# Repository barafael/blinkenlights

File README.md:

# blinkenlights: Blink lights and control other things, controlled by up to 5 input channels

The purpose of this board is to read some standard RC PWM channels, and switch the output MOSFETs accordingly.
This can be used to blink lights on an RC airplane in patterns, for example. The input channel allows to switch between modes, like standard flying mode and Taxi/Standby modes. Or, a landing light can be switched on/off by a separate channel.
The channels can be either dedicated lines from the receiver, or just other lines which are in use anyway. For example, the throttle signal could be used to switch between standby and flying, and the landing flaps signal could turn on/off the landing lights.

It would be easily possible to dim lights using PWM, I just have not made use of that yet.

The code pretty much just reads the input channels and reads the state from them, and then passes that state (and a tick value) to a function for each output pin. The function can then decide to do whatever with the output pin.

RC PWM signal is read using interrupts, and the program detects when a signal has been disconnected, resetting the state accordingly. That means that you can attach, detach, and reattach PWM signals during operation as you like.

The I2C pins are still free and accessible, so it would be possible to hook up I2C sensors also, like a temperature sensor on the brakes or a barometer.

Input voltage goes directly to the Pro Mini internal regulator, that means it should be 3.3V-16V.

That input voltage is directly supplied to the output pins via the MOSFET driver: an IRLML6244TRPBF SOT-23 package which can switch up to 6.3A (according to datasheet, but I haven't stressed it like that yet).

The PCB is designed in KiCad.

If you have any suggestions or spot an error somewhere, please let me know!

Render of PCB:

PCB in pcbnew:

Schematic:

MOSFET driver schematic:

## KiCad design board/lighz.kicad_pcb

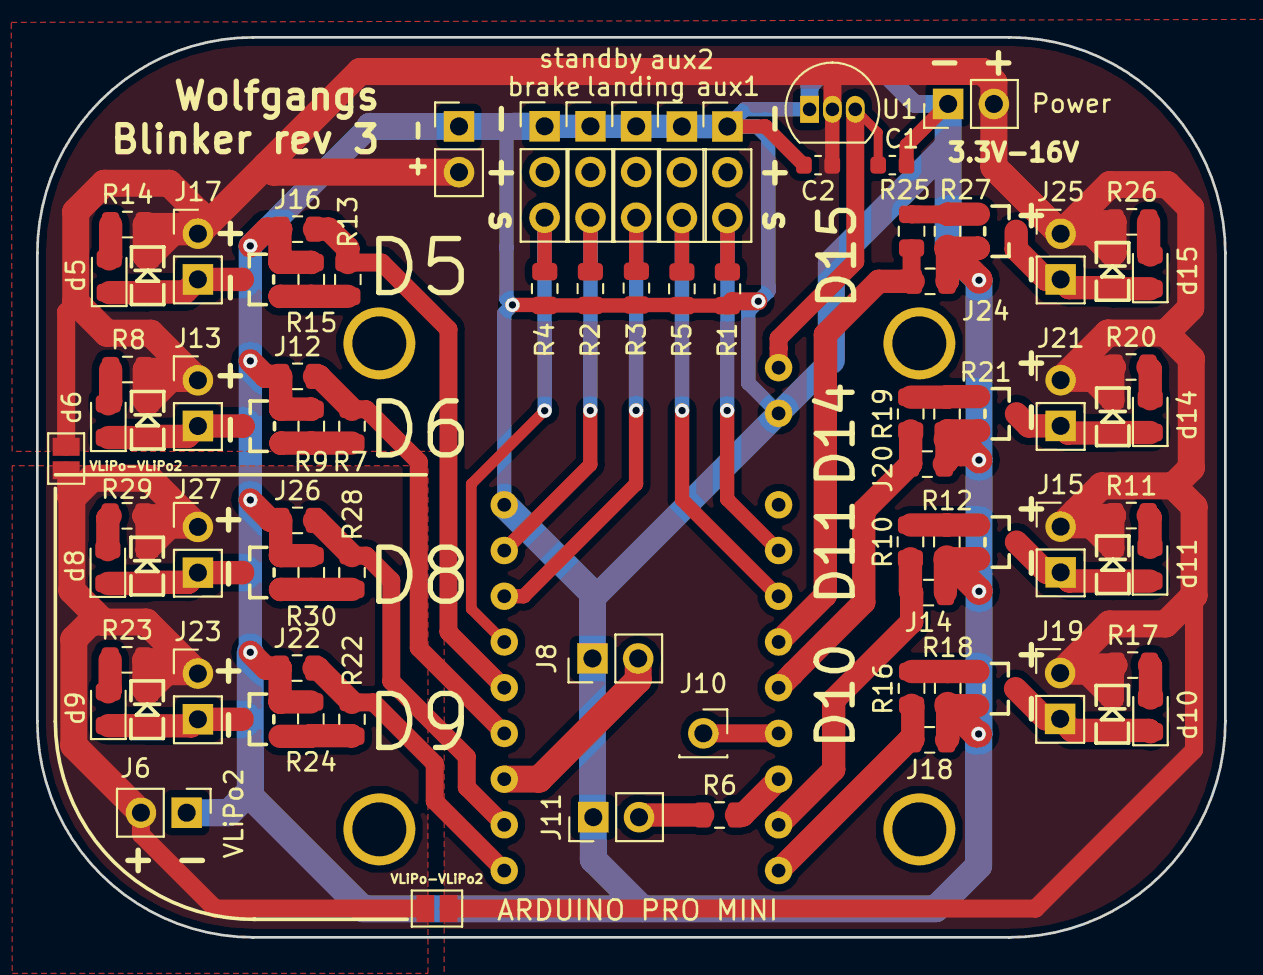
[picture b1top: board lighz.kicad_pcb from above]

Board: 2 copper layers, 66.0 x 50.0 mm, 91 parts (0 on the bottom side), 45 nets.

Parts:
1pin_prototyping, 1pin_prototyping#2, 1pin_prototyping#3, 1pin_prototyping#4: val**; 1pin_prototyping
C1, C2: C; C_0603_1608Metric
D2, D4, D6, D8, D10, D12, D14, D16: DIODE; LED-0805
J1: aux1; PinHeader_1x03_P2.54mm_Vertical
J2: brake; PinHeader_1x03_P2.54mm_Vertical
J3: aux2; PinHeader_1x03_P2.54mm_Vertical
J4: standby; PinHeader_1x03_P2.54mm_Vertical
J5: landing; PinHeader_1x03_P2.54mm_Vertical
J6: VLiPo2; PinHeader_1x02_P2.54mm_Vertical
J7: vlipo; PinHeader_1x02_P2.54mm_Vertical
J8: dbg2; PinHeader_1x02_P2.54mm_Vertical
J10: DBG_PIN; PinSocket_1x01_P2.54mm_Vertical
J11: buzz; PinHeader_1x02_P2.54mm_Vertical
J12, J14, J16, J18, J20, J22, J24, J26: Conn_01x02_Female; R_0805_2012Metric
J13, J15, J17, J19, J21, J23, J25, J27: output; PinHeader_1x02_P2.54mm_Vertical
Power: power; PinHeader_1x02_P2.54mm_Vertical
Q1, Q2, Q3, Q4, Q5, Q6, Q7, Q8: MOSFET_N; SOT23_FET
R1, R2, R3, R4, R5: R; R_0805_2012Metric
R6: 100; R_0805_2012Metric
R7, R10, R13, R16, R19, R22, R25, R28: 1k; R_0805_2012Metric
R8, R11, R14, R17, R20, R23, R26, R29: 500; R_0805_2012Metric
R9, R12, R15, R18, R21, R24, R27, R30: 100k; R_0805_2012Metric
U1: MCP1700-5002E_TO92; TO-92_Inline
VLiPo-VLiPo2, VLiPo-VLiPo2#2: R; SolderJumper-2_P1.3mm_Open_Pad1.0x1.5mm
d5, d6, d8, d9, d10, d11, d14, d15: LED; LED_0805_2012Metric
uP1: ARDUINO PRO MINI; ArduProMini-6

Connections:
D5_sig: J16.2, R13.2, uP1.14
D6_sig: J12.2, R7.2, uP1.15
D8_sig: J26.2, R28.2, uP1.17
D9_sig: J22.2, R22.2, uP1.18
D10_sig: J18.2, R16.2, uP1.30
D11_sig: J14.2, R10.2, uP1.29
D14_sig: J20.2, R19.2, uP1.26
D15_sig: J24.2, R25.2, uP1.25
GND: C1.2, C2.2, J1.1, J2.1, J3.1, J4.1, J5.1, J6.1, J7.1, J8.1, J11.1, J12.1, J14.1, J16.1, J18.1, J20.1, J22.1, J24.1, J26.1, Power.1, Q1.S, Q2.S, Q3.S, Q4.S, Q5.S, Q6.S, Q7.S, Q8.S, R1.2, R2.2, R3.2, R4.2, R5.2, R9.1, R12.1, R15.1, R18.1, R21.1, R24.1, R27.1, R30.1, U1.1, uP1.10, uP1.20
unnamed: C1.1, U1.3, uP1.19
unnamed: D2.A, J13.2, Q1.D, d6.1
unnamed: R8.2, d6.2
unnamed: D4.A, J15.2, Q2.D, d11.1
unnamed: R11.2, d11.2
unnamed: D6.A, J17.2, Q3.D, d5.1
unnamed: R14.2, d5.2
unnamed: D8.A, J19.2, Q4.D, d10.1
unnamed: R17.2, d10.2
unnamed: R20.2, d14.2
unnamed: D10.A, J21.2, Q5.D, d14.1
unnamed: D12.A, J23.2, Q6.D, d9.1
unnamed: R23.2, d9.2
unnamed: D14.A, J25.2, Q7.D, d15.1
unnamed: R26.2, d15.2
unnamed: D16.A, J27.2, Q8.D, d8.1
unnamed: R29.2, d8.2
unnamed: J1.3, R1.1, uP1.23
unnamed: J2.3, R4.1, uP1.13
unnamed: J3.3, R5.1, uP1.24
unnamed: J4.3, R2.1, uP1.11
unnamed: J5.3, R3.1, uP1.12
unnamed: J8.2, uP1.16
unnamed: J10.1, uP1.27
unnamed: J11.2, R6.1
unnamed: Q1.G, R7.1, R9.2
unnamed: Q2.G, R10.1, R12.2
unnamed: Q3.G, R13.1, R15.2
unnamed: Q4.G, R16.1, R18.2
unnamed: Q5.G, R19.1, R21.2
unnamed: Q6.G, R22.1, R24.2
unnamed: Q7.G, R25.1, R27.2
unnamed: Q8.G, R28.1, R30.2
unnamed: R6.2, uP1.28
VLiPo: C2.1, D2.K, D4.K, D6.K, D8.K, D10.K, D14.K, J7.2, J13.1, J15.1, J17.1, J19.1, J21.1, J25.1, Power.2, R8.1, R11.1, R14.1, R17.1, R20.1, R26.1, U1.2, VLiPo-VLiPo2.1, VLiPo-VLiPo2#2.1
VLiPo2: D12.K, D16.K, J6.2, J23.1, J27.1, R23.1, R29.1, VLiPo-VLiPo2.2, VLiPo-VLiPo2#2.2

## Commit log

2018-10-28 add blinker implementation
2018-10-28 add readme
2018-10-28 add board files
2018-10-28 update ignores to not ignore kicad lib files
2018-10-28 move microprocessor label silkscreen on PCB
2018-10-28 add images of board
2018-10-29 enable toggling modes while running
2018-10-29 add images of board to readme
2018-11-01 add pot, dbg pin
2018-11-02 use digitalio library and use fractions for cycle
2018-11-04 rename lighz to blinkenlights
2018-11-04 remove const qualifier, it was wrong
2018-11-04 remove possible data race
    write volatile variables only in interrupt
    read volatile variables only with disabled interrupts
2018-11-04 Add brake channel with PCInt
2018-11-04 pass state by reference, avoiding copy
2018-11-05 remove explicit mode enable
2018-11-05 s/flying_state_t/mode_t
2018-11-05 add new board revision
2018-11-05 update images for new board revision
2018-11-05 millis instead of delay
2018-11-05 formatting
2018-11-05 fix typo
2018-11-05 Add aux1/2 channels, fix PWM RC timeout
2018-11-05 prevent possible race condition for staleness detection
2018-11-05 Add pulse time short detection
2018-11-17 make stuff work again
2018-11-17 update net names and add v1->v2 lipo jumper
2018-11-18 new melody
2018-11-24 more realistic blink patterns
    and startup blink
2018-11-29 more realistic blink patterns
2018-11-30 add thermometer support
2018-12-03 add voltage regulator (5V MCP1700)
2018-12-03 add capacitors for voltage regulator
2019-04-09 rev 3 move around labels
2019-04-10 use analog pins for cooler leds
2019-04-10 remove possible data race
2019-04-10 currently deployed source
    ignore
2019-04-10 update images
2019-04-10 move file to avoid ino conflicts
2019-04-10 more switch statements
2019-04-10 add ideas.md
2020-10-06 Update LICENSE
